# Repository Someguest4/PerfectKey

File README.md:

# Perfectionist Keyboard
A project following the [HackClub KEEB project tutorial](https://keeb.hackclub.com/docs), making a custom mechanical keyboard from scratch.

I have always been a perfectionist and I often find myself following the lines between the keys on my keyboard instead of doing my homework so I decided to make a keyboard with perfectly aligned keys.

## What it is
An ortholinear TKL keyboard, designed from scratch in KiCad. All modifier keys are 2u, spacebar is 7u, board is 380x147fmm with a strip for the Pico, switches are on the normal 19.05mm grid, USB-C with a cutout in the case, just one stabilizer for the spacebar, because the footprints wouldn't fit directly above each other and it's not like the 2u keys will wobble enough to need a stabilizer :|

## Repo structure
- `kicad/` - schematic and PCB layout, Gerbers, drill files
- `case/` - case and plate files
- `photos/` - build photos for journal
- `firmware/` compiled ready to flash firmware
## Build log

**2026-07-11 - Schematic:**
Read through the guide and designed the schematic. Switch matrix, diodes so it doesn't ghost, stabs, wired it all to the Pico.

**2026-07-14 - Started placing switches:**

**2026-07-15 - Switches were completely wrong:**
Got the kicad-kbplacer plugin to place the keys instead and made the layout in KLE.

**2026-07-16 - Numbering everything:**
Had to number all the keys in KLE because kbplacer wouldn't place them correctly without an index, renamed all the rows and columns so it would recognize them.

**2026-07-17 - Routing:**
Routing cables and rerouting until they fit.

**2026-07-18 - Diodes, PCB finished:**
Kbplacer put the diodes inside the courtyards of the switches and the cables were so tight around them. I couldn't move them, so I had to reroute first. PCB finished after that.

**2026-07-22 - Starting the case:**
Started designing the case, rage quit because of Onshape (can't expect much from browser based software), switched to Fusion.

**2026-07-23 - Case, mostly finished:**
Did most of the case but no space for screw holes.

**2026-07-24 - Case finished:**
Made the case bigger so the holes fit and made the top plate removable.

## Firmware
I went with QMK since I used it for my hackpad. All handwired since it's a custom layout. Compiles clean, just waiting on the actual hardware to test.

## Status
Everything done, hoping and waiting for approval

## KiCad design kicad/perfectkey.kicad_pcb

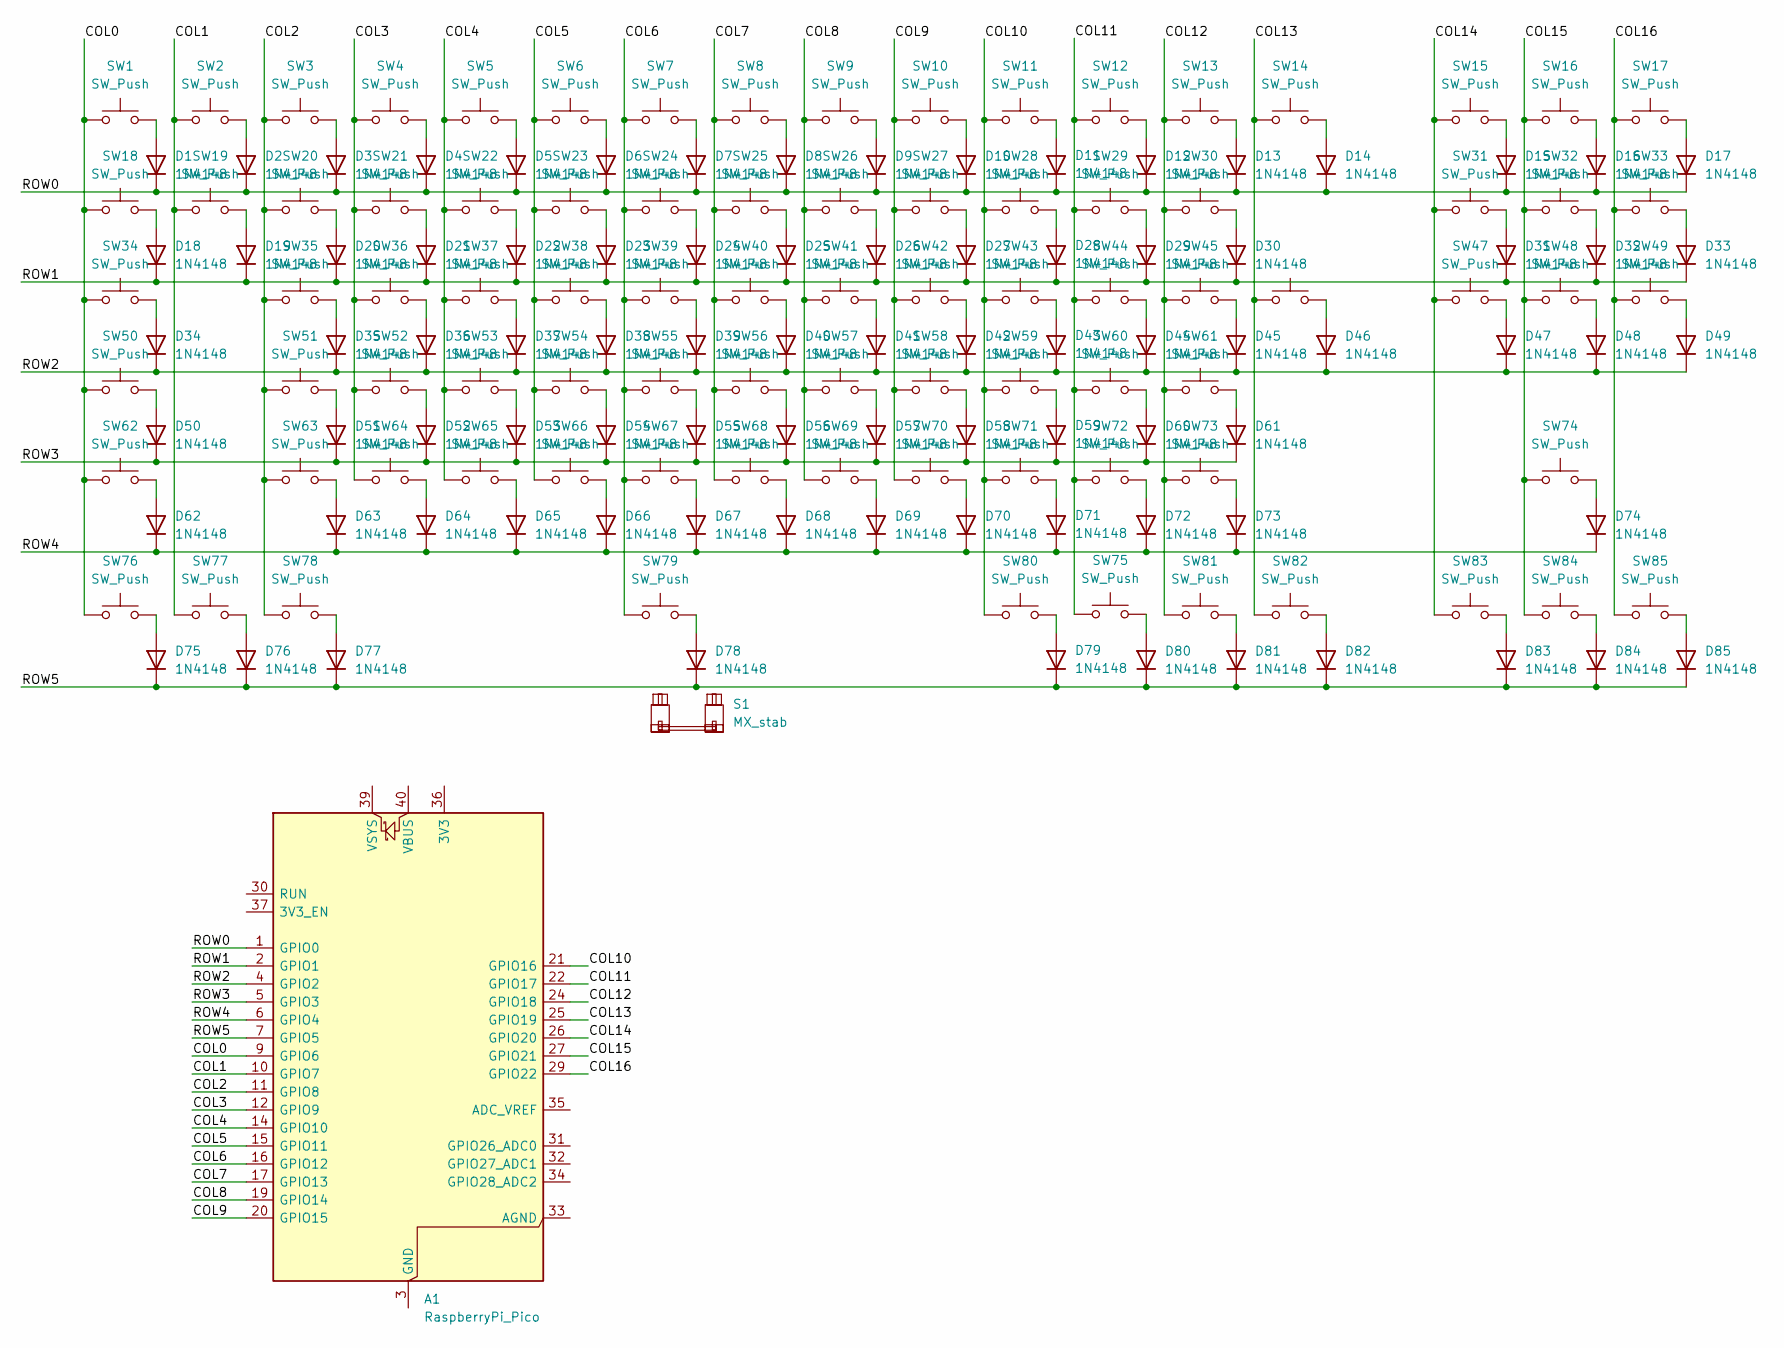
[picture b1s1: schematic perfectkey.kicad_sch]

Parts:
A1: RaspberryPi_Pico; RaspberryPi_Pico_Common_THT
D1, D2, D3, D4, D5, D6, D7, D8, D9, D10, D11, D12, D13, D14, D15, D16, D17, D18, D19, D20, D21, D22, D23, D24, D25, D26, D27, D28, D29, D30, D31, D32, D33, D34, D35, D36, D37, D38, D39, D40, D41, D42, D43, D44, D45, D46, D47, D48, D49, D50, D51, D52, D53, D54, D55, D56, D57, D58, D59, D60, D61, D62, D63, D64, D65, D66, D67, D68, D69, D70, D71, D72, D73, D74, D75, D76, D77, D78, D79, D80, D81, D82, D83, D84, D85: 1N4148; D_DO-35_SOD27_P7.62mm_Horizontal
S1: MX_stab; STAB_MX_7u
SW1, SW2, SW3, SW4, SW5, SW6, SW7, SW8, SW9, SW10, SW11, SW12, SW13, SW14, SW15, SW16, SW17, SW18, SW19, SW20, SW21, SW22, SW23, SW24, SW25, SW26, SW27, SW28, SW29, SW30, SW31, SW32, SW33, SW34, SW35, SW36, SW37, SW38, SW39, SW40, SW41, SW42, SW43, SW44, SW45, SW46, SW47, SW48, SW49, SW50, SW51, SW52, SW53, SW54, SW55, SW56, SW57, SW58, SW59, SW60, SW61, SW62, SW63, SW64, SW65, SW66, SW67, SW68, SW69, SW70, SW71, SW72, SW73, SW74, SW75, SW76, SW77, SW78, SW79, SW80, SW81, SW82, SW83, SW84, SW85: SW_Push; SW_MX_1u

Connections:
/COL0: A1.9 (GPIO6), SW1.1, SW18.1, SW34.1, SW50.1, SW62.1, SW76.1
/COL1: A1.10 (GPIO7), SW2.1, SW19.1, SW77.1
/COL2: A1.11 (GPIO8), SW3.1, SW20.1, SW35.1, SW51.1, SW63.1, SW78.1
/COL3: A1.12 (GPIO9), SW4.1, SW21.1, SW36.1, SW52.1, SW64.1
/COL4: A1.14 (GPIO10), SW5.1, SW22.1, SW37.1, SW53.1, SW65.1
/COL5: A1.15 (GPIO11), SW6.1, SW23.1, SW38.1, SW54.1, SW66.1
/COL6: A1.16 (GPIO12), SW7.1, SW24.1, SW39.1, SW55.1, SW67.1, SW79.1
/COL7: A1.17 (GPIO13), SW8.1, SW25.1, SW40.1, SW56.1, SW68.1
/COL8: A1.19 (GPIO14), SW9.1, SW26.1, SW41.1, SW57.1, SW69.1
/COL9: A1.20 (GPIO15), SW10.1, SW27.1, SW42.1, SW58.1, SW70.1
/COL10: A1.21 (GPIO16), SW11.1, SW28.1, SW43.1, SW59.1, SW71.1, SW80.1
/COL11: A1.22 (GPIO17), SW12.1, SW29.1, SW44.1, SW60.1, SW72.1, SW75.1
/COL12: A1.24 (GPIO18), SW13.1, SW30.1, SW45.1, SW61.1, SW73.1, SW81.1
/COL13: A1.25 (GPIO19), SW14.1, SW46.1, SW82.1
/COL14: A1.26 (GPIO20), SW15.1, SW31.1, SW47.1, SW83.1
/COL15: A1.27 (GPIO21), SW16.1, SW32.1, SW48.1, SW74.1, SW84.1
/COL16: A1.29 (GPIO22), SW17.1, SW33.1, SW49.1, SW85.1
/ROW0: A1.1 (GPIO0), D1.1 (K), D2.1 (K), D3.1 (K), D4.1 (K), D5.1 (K), D6.1 (K), D7.1 (K), D8.1 (K), D9.1 (K), D10.1 (K), D11.1 (K), D12.1 (K), D13.1 (K), D14.1 (K), D15.1 (K), D16.1 (K), D17.1 (K)
/ROW1: A1.2 (GPIO1), D18.1 (K), D19.1 (K), D20.1 (K), D21.1 (K), D22.1 (K), D23.1 (K), D24.1 (K), D25.1 (K), D26.1 (K), D27.1 (K), D28.1 (K), D29.1 (K), D30.1 (K), D31.1 (K), D32.1 (K), D33.1 (K)
/ROW2: A1.4 (GPIO2), D34.1 (K), D35.1 (K), D36.1 (K), D37.1 (K), D38.1 (K), D39.1 (K), D40.1 (K), D41.1 (K), D42.1 (K), D43.1 (K), D44.1 (K), D45.1 (K), D46.1 (K), D47.1 (K), D48.1 (K), D49.1 (K)
/ROW3: A1.5 (GPIO3), D50.1 (K), D51.1 (K), D52.1 (K), D53.1 (K), D54.1 (K), D55.1 (K), D56.1 (K), D57.1 (K), D58.1 (K), D59.1 (K), D60.1 (K), D61.1 (K)
/ROW4: A1.6 (GPIO4), D62.1 (K), D63.1 (K), D64.1 (K), D65.1 (K), D66.1 (K), D67.1 (K), D68.1 (K), D69.1 (K), D70.1 (K), D71.1 (K), D72.1 (K), D73.1 (K), D74.1 (K)
/ROW5: A1.7 (GPIO5), D75.1 (K), D76.1 (K), D77.1 (K), D78.1 (K), D79.1 (K), D80.1 (K), D81.1 (K), D82.1 (K), D83.1 (K), D84.1 (K), D85.1 (K)
unnamed: A1.3 (GND), A1.8 (GND), A1.13 (GND), A1.18 (GND), A1.23 (GND), A1.28 (GND), A1.38 (GND)
unnamed: D1.2 (A), SW1.2
unnamed: D2.2 (A), SW2.2
unnamed: D3.2 (A), SW3.2
unnamed: D4.2 (A), SW4.2
unnamed: D5.2 (A), SW5.2
unnamed: D6.2 (A), SW6.2
unnamed: D7.2 (A), SW7.2
unnamed: D8.2 (A), SW8.2
unnamed: D9.2 (A), SW9.2
unnamed: D10.2 (A), SW10.2
unnamed: D11.2 (A), SW11.2
unnamed: D12.2 (A), SW12.2
unnamed: D13.2 (A), SW13.2
unnamed: D14.2 (A), SW14.2
unnamed: D15.2 (A), SW15.2
unnamed: D16.2 (A), SW16.2
unnamed: D17.2 (A), SW17.2
unnamed: D18.2 (A), SW18.2
unnamed: D19.2 (A), SW19.2
unnamed: D20.2 (A), SW20.2
unnamed: D21.2 (A), SW21.2
unnamed: D22.2 (A), SW22.2
unnamed: D23.2 (A), SW23.2
unnamed: D24.2 (A), SW24.2
unnamed: D25.2 (A), SW25.2
unnamed: D26.2 (A), SW26.2
unnamed: D27.2 (A), SW27.2
unnamed: D28.2 (A), SW28.2
unnamed: D29.2 (A), SW29.2
unnamed: D30.2 (A), SW30.2
unnamed: D31.2 (A), SW31.2
unnamed: D32.2 (A), SW32.2
unnamed: D33.2 (A), SW33.2
unnamed: D34.2 (A), SW34.2
unnamed: D35.2 (A), SW35.2
unnamed: D36.2 (A), SW36.2
unnamed: D37.2 (A), SW37.2
unnamed: D38.2 (A), SW38.2
unnamed: D39.2 (A), SW39.2
unnamed: D40.2 (A), SW40.2
unnamed: D41.2 (A), SW41.2
unnamed: D42.2 (A), SW42.2
unnamed: D43.2 (A), SW43.2
unnamed: D44.2 (A), SW44.2
unnamed: D45.2 (A), SW45.2
unnamed: D46.2 (A), SW46.2
unnamed: D47.2 (A), SW47.2
unnamed: D48.2 (A), SW48.2
unnamed: D49.2 (A), SW49.2
unnamed: D50.2 (A), SW50.2
unnamed: D51.2 (A), SW51.2
unnamed: D52.2 (A), SW52.2
unnamed: D53.2 (A), SW53.2
unnamed: D54.2 (A), SW54.2
unnamed: D55.2 (A), SW55.2
unnamed: D56.2 (A), SW56.2
unnamed: D57.2 (A), SW57.2
unnamed: D58.2 (A), SW58.2
unnamed: D59.2 (A), SW59.2
unnamed: D60.2 (A), SW60.2
unnamed: D61.2 (A), SW61.2
unnamed: D62.2 (A), SW62.2
unnamed: D63.2 (A), SW63.2
unnamed: D64.2 (A), SW64.2
unnamed: D65.2 (A), SW65.2
unnamed: D66.2 (A), SW66.2
unnamed: D67.2 (A), SW67.2
unnamed: D68.2 (A), SW68.2
unnamed: D69.2 (A), SW69.2
unnamed: D70.2 (A), SW70.2
unnamed: D71.2 (A), SW71.2
unnamed: D72.2 (A), SW72.2
unnamed: D73.2 (A), SW73.2
unnamed: D74.2 (A), SW74.2
unnamed: D75.2 (A), SW76.2
unnamed: D76.2 (A), SW77.2
unnamed: D77.2 (A), SW78.2
unnamed: D78.2 (A), SW79.2
unnamed: D79.2 (A), SW80.2
unnamed: D80.2 (A), SW75.2
unnamed: D81.2 (A), SW81.2
unnamed: D82.2 (A), SW82.2
unnamed: D83.2 (A), SW83.2
unnamed: D84.2 (A), SW84.2
unnamed: D85.2 (A), SW85.2

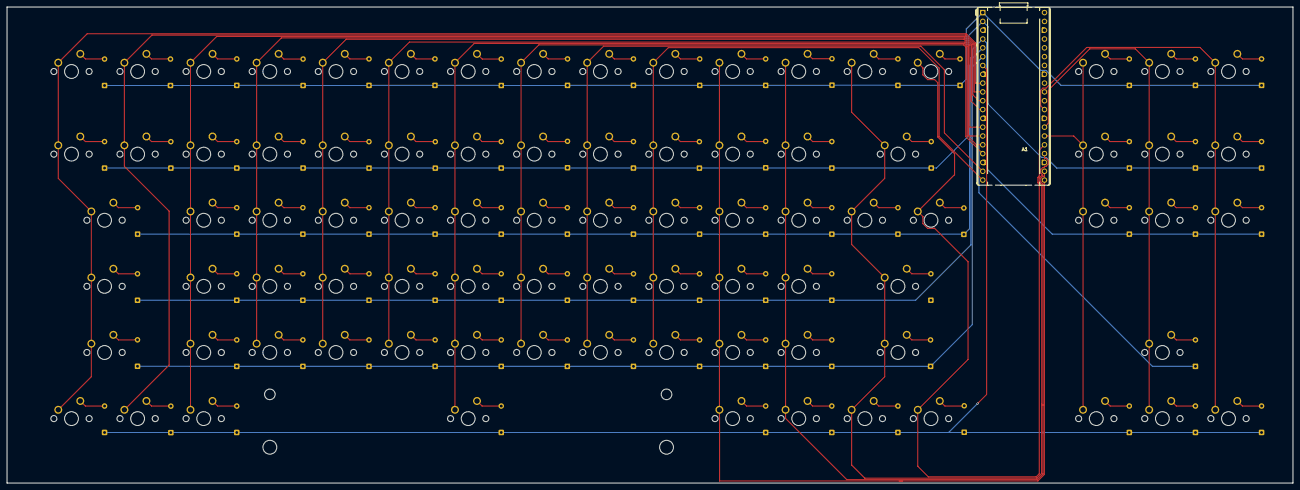
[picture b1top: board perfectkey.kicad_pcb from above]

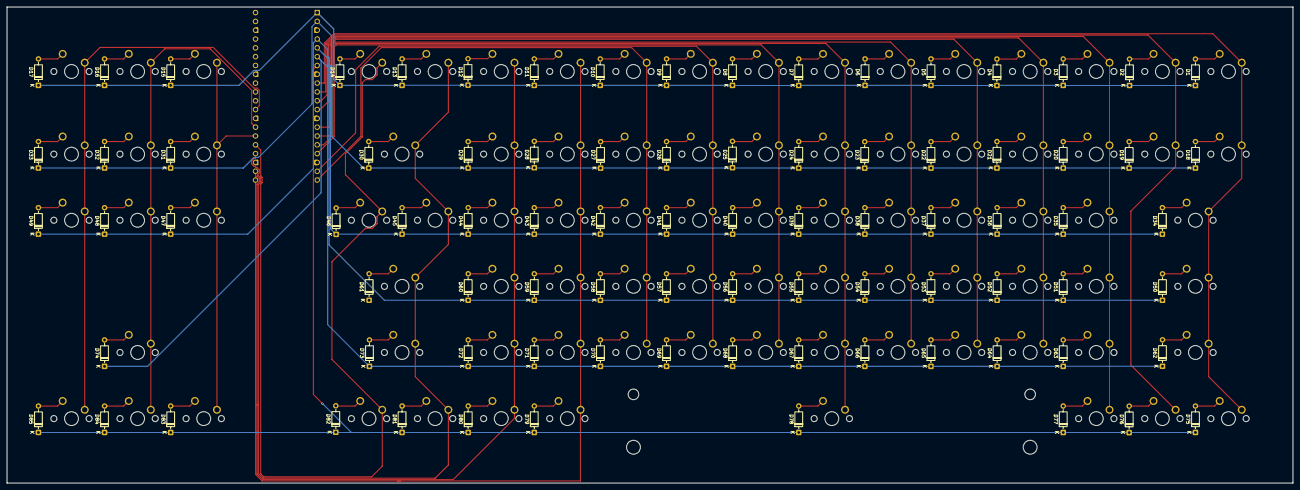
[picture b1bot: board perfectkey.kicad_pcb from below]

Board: 2 copper layers, 370.5 x 137.2 mm, 172 parts (85 on the bottom side), 109 nets.
